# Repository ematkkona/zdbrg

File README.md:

zdbrg - Antenna rotator for receiving HRPT/HRIT -LEO satellite transmissions (Meteor M-2, NOAA-15/18/19 & MetOp etc)

* Raspberry Pi Zero (W) as main controller, running a super light buildroot-based OS.
  All wireless features are disabled by default.
* Custom PCB for neatly connecting everything together and handling serial communiaction
* Mostly 3d printed structural parts
*  Antenna center frequency 1700MHz (RHCP)
* EasyCommV2 compatible for use with 'rotctld'
* NEMA17 stepper motors: 0,9deg, 1.5A, 400SPR with full-step torque of 1,2NM.
  A4988 driver circuis.
  Printed 5:1 planetary reduction gears used for increased torque and better resistance
  against non-controlled, free movement while motors are disabled.

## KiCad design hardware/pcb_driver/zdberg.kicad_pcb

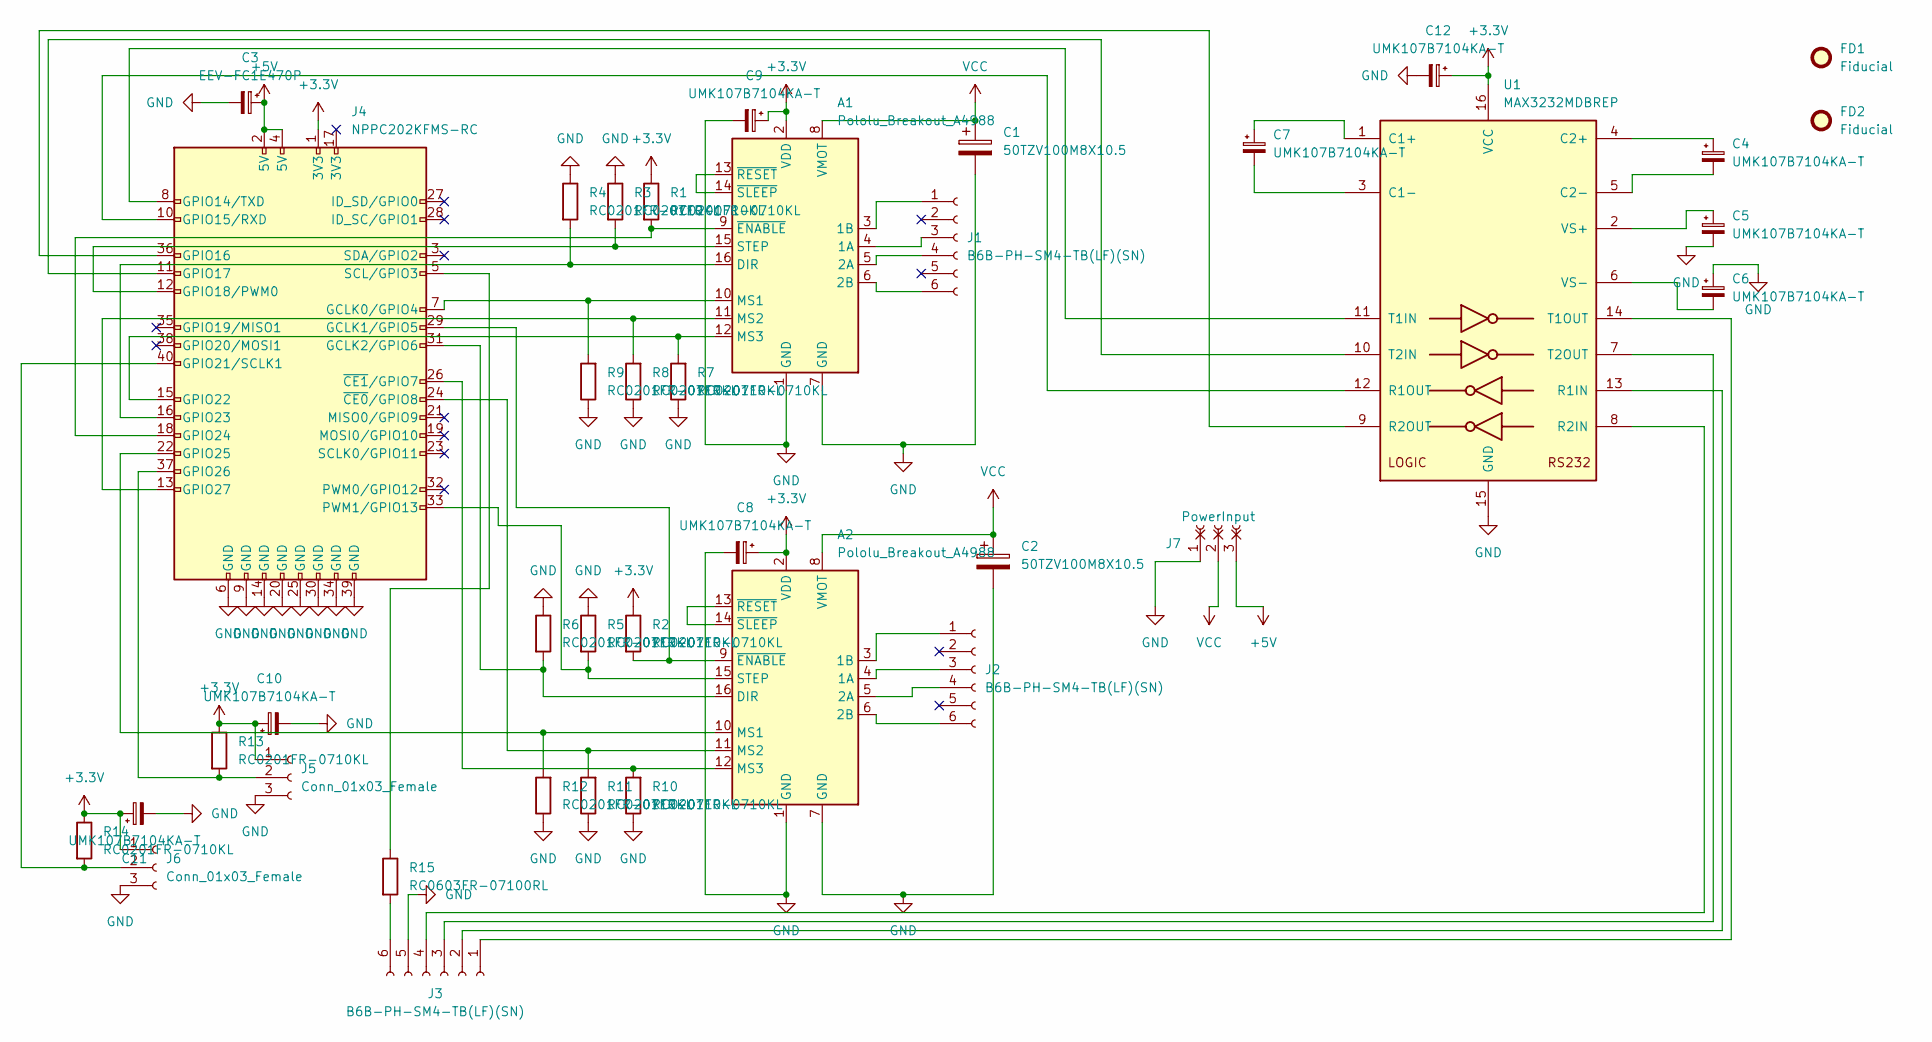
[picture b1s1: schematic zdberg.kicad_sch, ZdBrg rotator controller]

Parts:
A1, A2: Pololu_Breakout_A4988; Pololu_Breakout-16_15.2x20.3mm
C1, C2: 50TZV100M8X10.5; CP_Elec_8x10.5
C3: EEV-FC1E470P; CP_Elec_8x6.2
C4, C5, C6, C7, C8, C9, C10, C11, C12: UMK107B7104KA-T; C_0603_1608Metric
FD1, FD2: Fiducial; Fiducial_1.5mm_Mask3mm
J1, J2, J3: B6B-PH-SM4-TB(LF)(SN); JST_PH_B6B-PH-SM4-TB_1x06-1MP_P2.00mm_Vertical
J4: NPPC202KFMS-RC; PinSocket_2x20_P2.54mm_Vertical_SMD
J5, J6: Conn_01x03_Female; FanPinHeader_1x03_P2.54mm_Vertical
J7: PowerInput; Molex_KK-396_5273-03A_1x03_P3.96mm_Vertical
R1, R2, R3, R4, R5, R6, R7, R8, R9, R10, R11, R12, R13, R14: RC0201FR-0710KL; R_0201_0603Metric
R15: RC0603FR-07100RL; R_0603_1608Metric
U1: MAX3232MDBREP; SSOP-16_4.4x5.2mm_P0.65mm

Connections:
+3.3V: A1.2 (VDD), A2.2 (VDD), C8.1, C9.1, C10.1, C11.1, C12.1, J4.1 (3V3), J5.1, J6.1, R1.1, R2.1, R13.1, R14.1, U1.16 (VCC)
+5V: C3.1, J4.2 (5V), J4.4 (5V), J7.3
GND: A1.1 (GND), A1.7 (GND), A2.1 (GND), A2.7 (GND), C1.2, C2.2, C3.2, C5.2, C6.1, C8.2, C9.2, C10.2, C11.2, C12.2, J3.5, J4.6 (GND), J4.9 (GND), J4.14 (GND), J4.20 (GND), J4.25 (GND), J4.30 (GND), J4.34 (GND), J4.39 (GND), J5.3, J6.3, J7.1, R3.1, R4.1, R5.1, R6.1, R7.1, R8.1, R9.1, R10.1, R11.1, R12.1, U1.15 (GND)
unnamed: A1.3 (1B), J1.1
unnamed: A1.4 (1A), J1.3
unnamed: A1.5 (2A), J1.4
unnamed: A1.6 (2B), J1.6
unnamed: A1.9 (~ENABLE), J4.18 (GPIO24), R1.2
unnamed: A1.10 (MS1), J4.7 (GCLK0/GPIO4), R9.2
unnamed: A1.11 (MS2), J4.13 (GPIO27), R8.2
unnamed: A1.12 (MS3), J4.15 (GPIO22), R7.2
unnamed: A1.13 (~RESET), A1.14 (~SLEEP)
unnamed: A1.15 (STEP), J4.12 (GPIO18/PWM0), R3.2
unnamed: A1.16 (DIR), J4.16 (GPIO23), R4.2
unnamed: A2.3 (1B), J2.1
unnamed: A2.4 (1A), J2.3
unnamed: A2.5 (2A), J2.4
unnamed: A2.6 (2B), J2.6
unnamed: A2.9 (~ENABLE), J4.29 (GCLK1/GPIO5), R2.2
unnamed: A2.10 (MS1), J4.22 (GPIO25), R12.2
unnamed: A2.11 (MS2), J4.24 (~CE0/GPIO8), R11.2
unnamed: A2.12 (MS3), J4.26 (~CE1/GPIO7), R10.2
unnamed: A2.13 (~RESET), A2.14 (~SLEEP)
unnamed: A2.15 (STEP), J4.33 (PWM1/GPIO13), R5.2
unnamed: A2.16 (DIR), J4.31 (GCLK2/GPIO6), R6.2
unnamed: C4.1, U1.4 (C2+)
unnamed: C4.2, U1.5 (C2-)
unnamed: C5.1, U1.2 (VS+)
unnamed: C6.2, U1.6 (VS-)
unnamed: C7.1, U1.1 (C1+)
unnamed: C7.2, U1.3 (C1-)
unnamed: J3.1, U1.14 (T1OUT)
unnamed: J3.2, U1.13 (R1IN)
unnamed: J3.3, U1.7 (T2OUT)
unnamed: J3.4, U1.8 (R2IN)
unnamed: J3.6, R15.2
unnamed: J4.5 (SCL/GPIO3), R15.1
unnamed: J4.8 (GPIO14/TXD), U1.11 (T1IN)
unnamed: J4.10 (GPIO15/RXD), U1.12 (R1OUT)
unnamed: J4.11 (GPIO17), U1.10 (T2IN)
unnamed: J4.36 (GPIO16), U1.9 (R2OUT)
unnamed: J4.37 (GPIO26), J5.2, R13.2
unnamed: J4.40 (GPIO21/SCLK1), J6.2, R14.2
VCC: A1.8 (VMOT), A2.8 (VMOT), C1.1, C2.1, J7.2

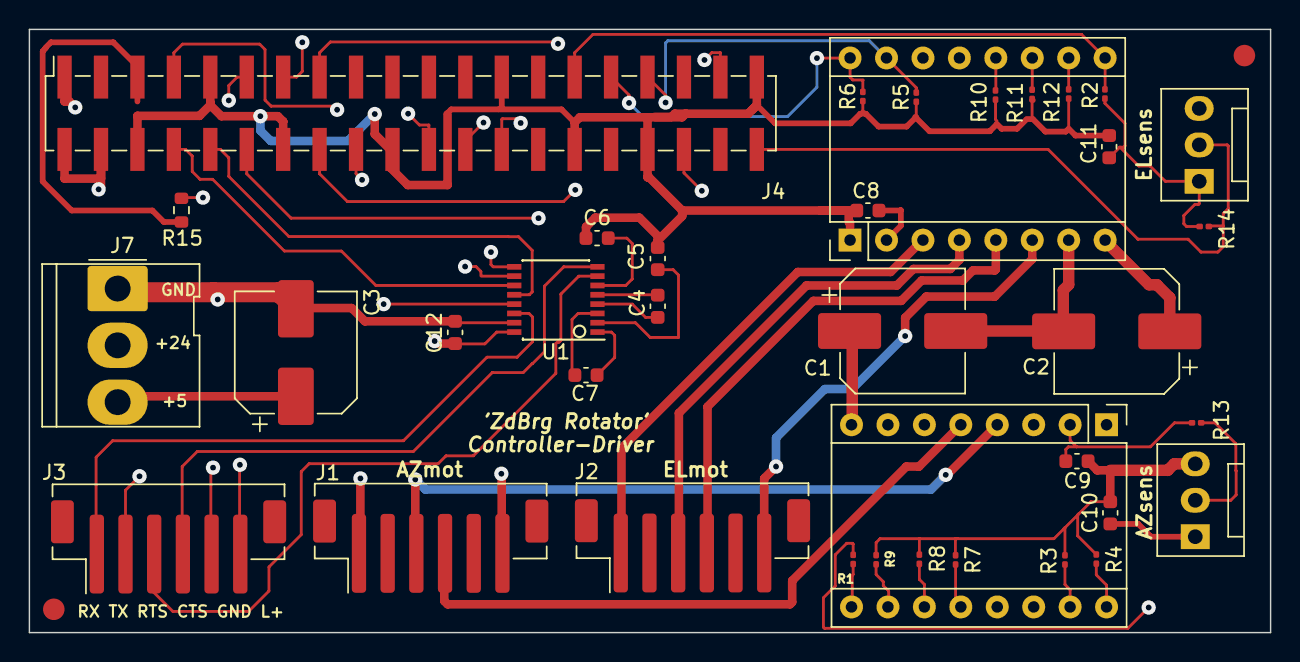
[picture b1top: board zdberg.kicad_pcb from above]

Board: 4 copper layers, 86.5 x 42.0 mm, 39 parts (0 on the bottom side), 44 nets.

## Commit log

2022-11-18 Overhaul
2022-11-18 Fix'd
2022-11-19 Buildroot defconfig
    Added (rpi0w) defconfig for simpler build process
